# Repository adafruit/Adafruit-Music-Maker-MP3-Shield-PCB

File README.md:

# Adafruit Music Maker MP3 Shields PCB

&nbsp; <br />
Click to purchase from the Adafruit Shop:
- [With 3W Amp](https://www.adafruit.com/product/1788)
- [Without 3W Amp](https://www.adafruit.com/product/1790)

These powerful shields feature the VS1053, an encoding/decoding (codec) chip that can decode a wide variety of audio formats such as MP3, AAC, Ogg Vorbis, WMA, MIDI, FLAC, WAV (PCM and ADPCM). They can also be used to record audio in both PCM (WAV) and compressed Ogg Vorbis. You can do all sorts of stuff with the audio as well such as adjusting bass, treble, and volume digitally.

All this functionality is implemented in a light-weight SPI interface so that any Arduino can play audio from an SD card. There's also a special MIDI mode that you can boot the chip into that will read 'classic' 31250Kbaud MIDI data from an Arduino pin and act like a synth/drum machine - there are dozens of built-in drum and sample effects! But the chip is a pain to solder, and needs a lot of extras. That's why we spun up the best shields, perfect for use with any Adafruit Metro or Arduino Uno, Leonardo or Mega.

There are two versions of the shield: the first has stereo line/headphone output. There is also a version with a 3W/channel class-D stereo speaker amplifier for easy use in projects that need to be loud.

Yjis repo contains PCB files for the Adafruit Music Maker VS1053 (MP3/MIDI/WAV/Ogg...) Shields for Arduino

Format is EagleCAD schematic and board layout

For more details, check out the product pages at

-----> https://www.adafruit.com/product/1788

-----> https://www.adafruit.com/product/1790

Revision history:

* As of Aug 23, 2023 - we've updated this PCB with Adafruit Pinguin to make a lovely and legible silkscreen. We've also updated the music maker to use the 2x3 SPI header instead of pins 11/12/13  and the terminal blocks now come pre-soldered on.
* Aug 20, 2014: We updated the analog section to have more filtering, which should improve audio output quality (even more!) There are no wiring or code changes.

### License

Adafruit invests time and resources providing this open source design, please support Adafruit and open-source hardware by purchasing products from [Adafruit](https://www.adafruit.com)!

All text above must be included in any redistribution

Designed by Limor Fried/Ladyada for Adafruit Industries.
Creative Commons Attribution/Share-Alike, all text above must be included in any redistribution. 
See license.txt for additional information.

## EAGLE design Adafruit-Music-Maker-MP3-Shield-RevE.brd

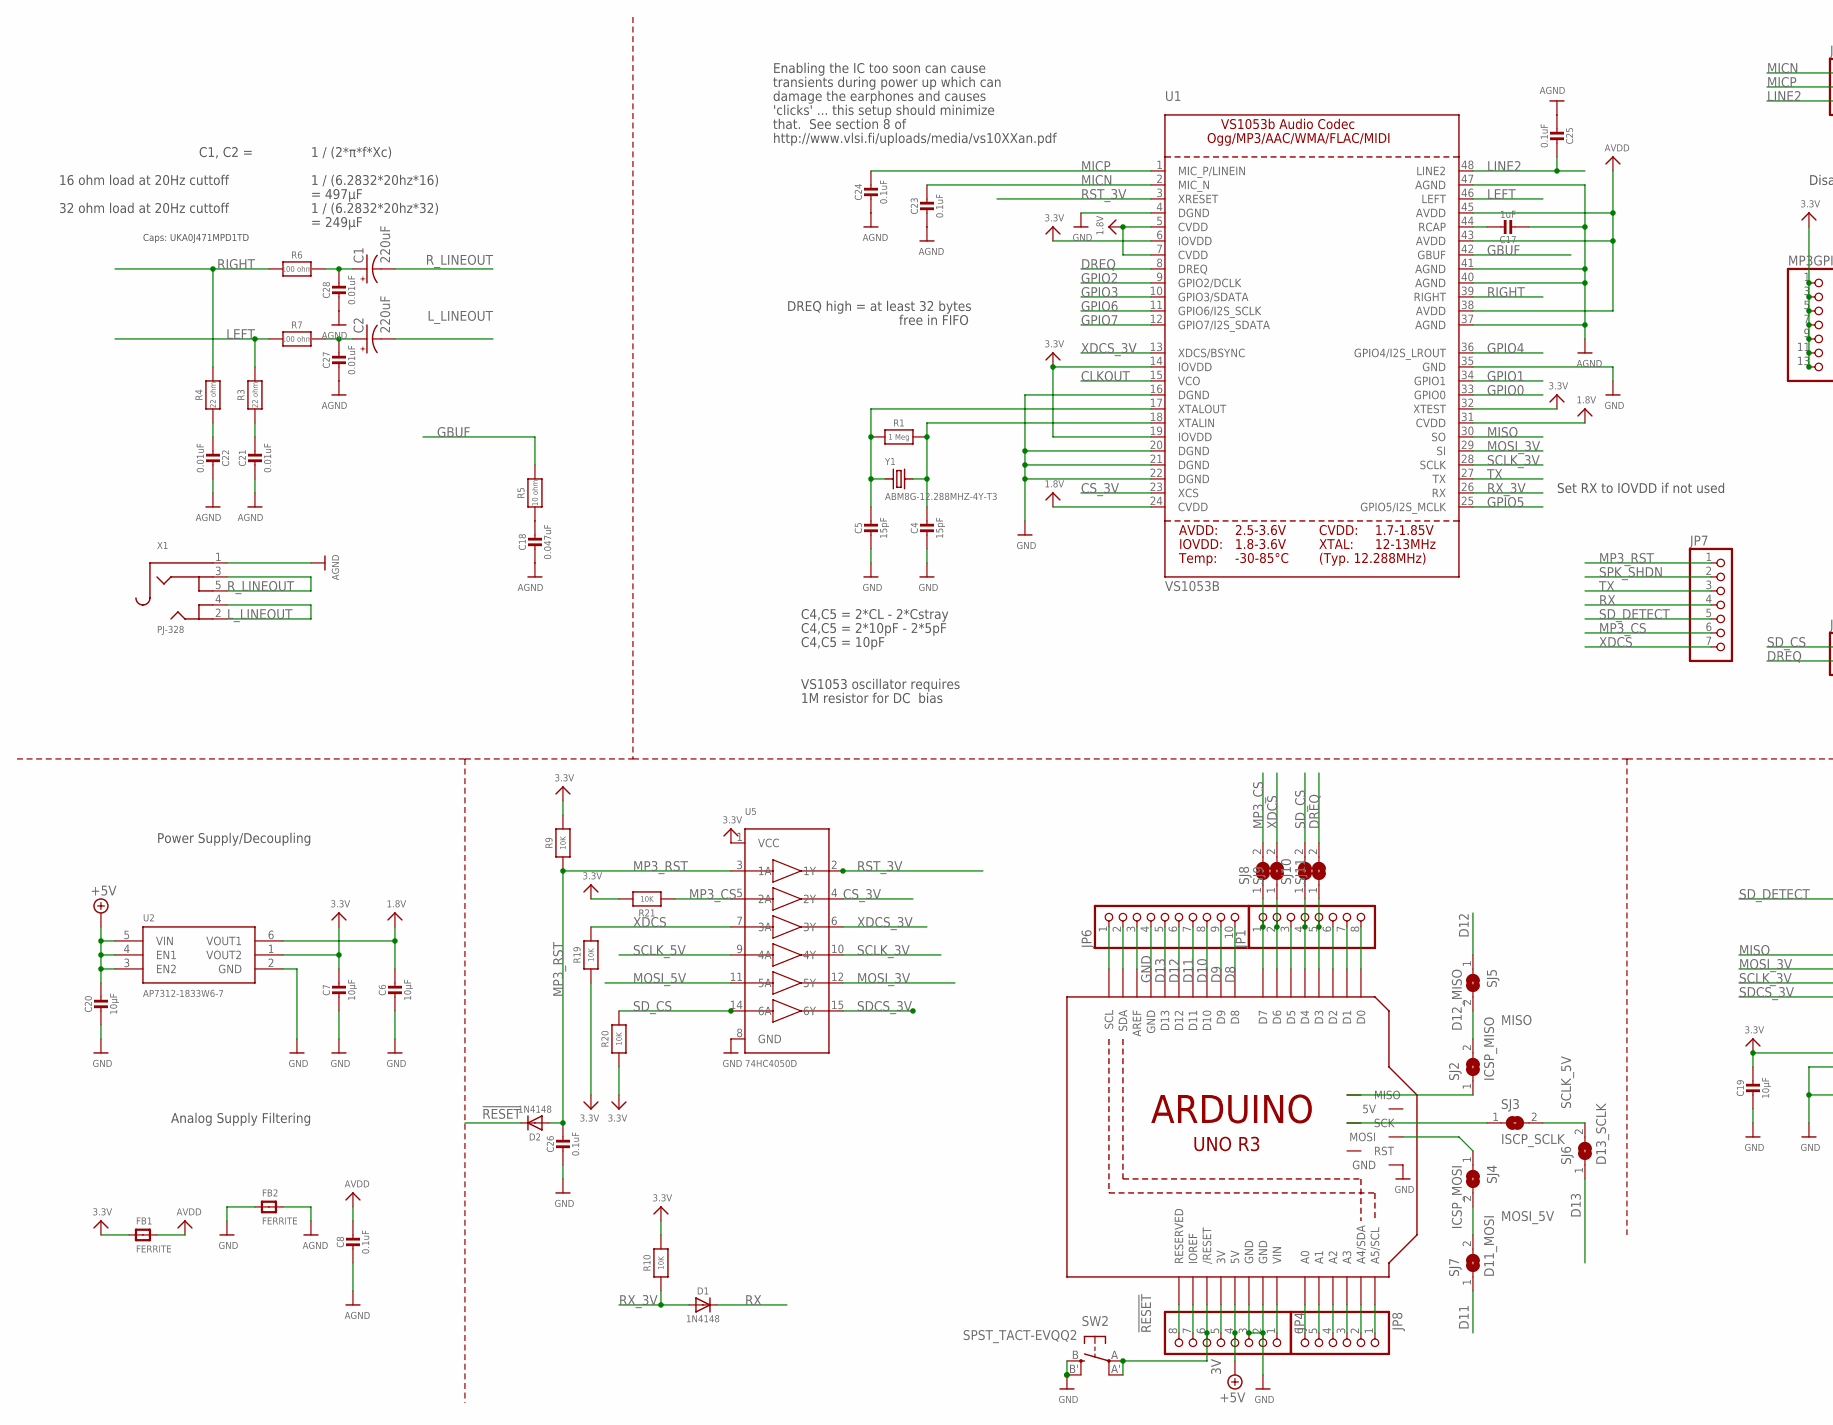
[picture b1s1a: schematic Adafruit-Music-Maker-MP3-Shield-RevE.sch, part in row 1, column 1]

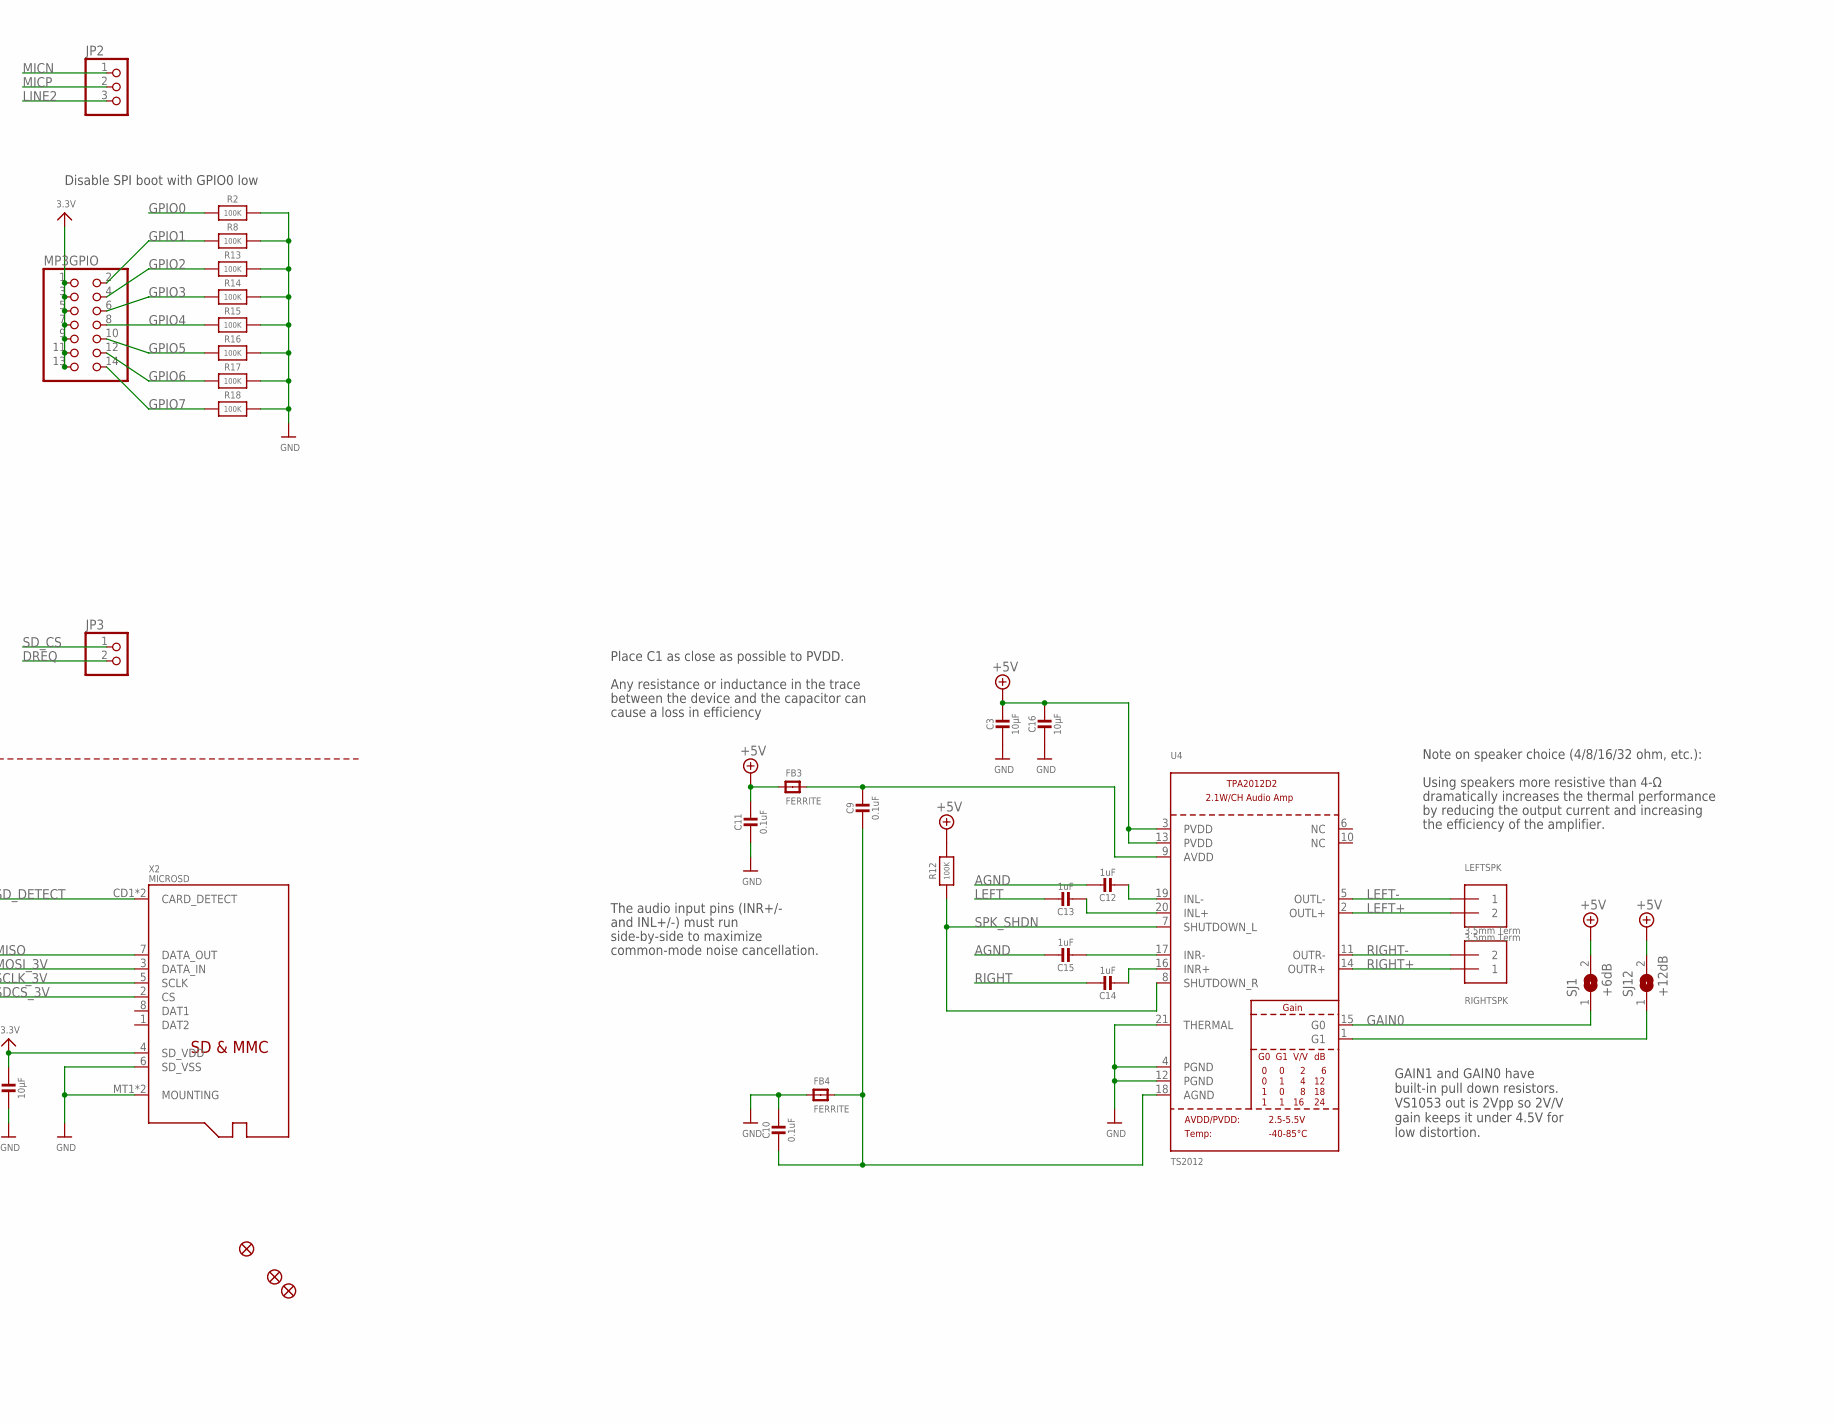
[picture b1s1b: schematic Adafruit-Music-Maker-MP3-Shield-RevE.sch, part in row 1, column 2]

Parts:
C1, C2: 220uF; PANASONIC_C
C3, C6, C7, C16, C19, C20: 10µF; 0805-NO
C4, C5: 15pF; 0603-NO
C8, C9, C10, C11, C23, C24, C25, C26: 0.1uF; 0603-NO
C12, C13, C14, C15, C17: 1uF; 0603-NO
C18: 0.047uF; 0603-NO
C21, C22, C27, C28: 0.01uF; 0603-NO
D1, D2: 1N4148; SOD-323
FB1, FB2, FB3, FB4: FERRITE; 0603-NO
FID1, FID2, FID3: FIDUCIAL_1MM
JP1, JP4: PINHD-1X8CLEANBIG; 1X08-CLEANBIG
JP2: PINHD-1X3CB; 1X03-CLEANBIG
JP3: HEADER-1X2ROUND; 1X02_ROUND
JP6: HEADER-1X1070MIL; 1X10_ROUND70
JP7: HEADER-1X770MIL; 1X07_ROUND_70
JP8: PINHD-1X6CB; 1X06-CLEANBIG
LEFTSPK: 3.5mm Term; TERMBLOCK_1X2-3.5MM
MP3GPIO: HEADER-2X7_ROUND_70MIL; 2X07_ROUND_70MIL
R1: 1 Meg; 0603-NO
R2, R8, R12, R13, R14, R15, R16, R17, R18: 100K; 0603-NO
R3, R4: 22 ohm; 0603-NO
R5: 10 ohm; 0603-NO
R6, R7: 100 ohm; 0603-NO
R9, R10, R19, R20, R21: 10K; 0603-NO
RIGHTSPK: 3.5mm Term; TERMBLOCK_1X2-3.5MM
SJ1: +6dB; SOLDERJUMPER_ARROW_NOPASTE
SJ2: ICSP_MISO; SOLDERJUMPER_CLOSEDWIRE
SJ3: ISCP_SCLK; SOLDERJUMPER_CLOSEDWIRE
SJ4: ICSP_MOSI; SOLDERJUMPER_CLOSEDWIRE
SJ5: D12_MISO; SOLDERJUMPER_ARROW_NOPASTE
SJ6: D13_SCLK; SOLDERJUMPER_ARROW_NOPASTE
SJ7: D11_MOSI; SOLDERJUMPER_ARROW_NOPASTE
SJ8, SJ9, SJ10, SJ11: SOLDERJUMPERCLOSED; SOLDERJUMPER_CLOSEDWIRE
SJ12: +12dB; SOLDERJUMPER_ARROW_NOPASTE
SW2: SPST_TACT-EVQQ2; EVQ-Q2
U1: VS1053B; LQFP48
U2: AP7312-1833W6-7; SOT23-6
U4: TS2012; WQFN20
U5: 74HC4050D; SOIC16
U$41: ARDUINO_R3_ICSP; ARDUINOR3_ICSP
X1: PJ-328; PJ-328-5
X2: MICROSD
Y1: ABM8G-12.288MHZ-4Y-T3; CRYSTAL_3.2X2.5

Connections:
1.8V: C6.1, U1.5 (CVDD), U1.7 (CVDD), U1.24 (CVDD), U1.31 (CVDD), U2.6 (VOUT1)
3.3V: C7.1, C19.1, FB1.1, MP3GPIO.1, MP3GPIO.3, MP3GPIO.5, MP3GPIO.7, MP3GPIO.9, MP3GPIO.11, MP3GPIO.13, R9.2, R10.2, R19.1, R20.1, R21.2, U1.6 (IOVDD), U1.14 (IOVDD), U1.19 (IOVDD), U1.32 (XTEST), U2.1 (VOUT2), U5.1 (VCC), X2.4 (SD_VDD)
3V: JP4.5, U$41.3V
!RESET: D2.C, JP4.6, SW2.A, SW2.A' (P1), U$41.RESET (/RESET)
+5V: C3.1, C11.1, C16.1, C20.1, FB3.1, JP4.4, R12.2, SJ1.2, SJ12.2, U2.3 (EN2), U2.4 (EN1), U2.5 (VIN), U4.3 (PVDD), U4.13 (PVDD), U$41.5V
A0: JP8.6, U$41.A0
A1: JP8.5, U$41.A1
A2: JP8.4, U$41.A2
A3: JP8.3, U$41.A3
A4: JP8.2, U$41.A4 (A4/SDA)
A5: JP8.1, U$41.A5 (A5/SCL)
AGND: C8.2, C12.1, C15.1, C17.2, C18.2, C21.2, C22.2, C23.2, C24.2, C25.2, C27.2, C28.2, FB2.2, U1.37 (AGND), U1.40 (AGND), U1.41 (AGND), U1.47 (AGND), X1.1
AREF: JP6.3, U$41.AREF
AVDD: C8.1, FB1.2, U1.38 (AVDD), U1.43 (AVDD), U1.45 (AVDD)
CLKOUT: U1.15 (VCO)
CS_3V: U1.23 (XCS), U5.4 (2Y)
D0: JP1.8, U$41.D0
D1: JP1.7, U$41.D1
D2: JP1.6, U$41.D2
D3: JP1.5, SJ11.1, U$41.D3
D4: JP1.4, SJ10.1, U$41.D4
D5: JP1.3, U$41.D5
D6: JP1.2, SJ9.1, U$41.D6
D7: JP1.1, SJ8.1, U$41.D7
D8: JP6.10, U$41.D8
D9: JP6.9, U$41.D9
D10: JP6.8, U$41.D10
D11: JP6.7, SJ7.1, U$41.D11
D12: JP6.6, SJ5.1, U$41.D12
D13: JP6.5, SJ6.1, U$41.D13
DREQ: JP3.2, SJ11.2, U1.8 (DREQ)
GAIN0: SJ1.1, U4.15 (G0)
GBUF: R5.1, U1.42 (GBUF)
GND: C3.2, C4.2, C5.2, C6.2, C7.2, C10.1, C11.2, C16.2, C19.2, C20.2, C26.2, FB2.1, FB4.1, JP4.2, JP4.3, JP6.4, R2.2, R8.2, R13.2, R14.2, R15.2, R16.2, R17.2, R18.2, SW2.B (S), SW2.B' (S1), U1.4 (DGND), U1.16 (DGND), U1.20 (DGND), U1.21 (DGND), U1.22 (DGND), U1.35 (GND), U2.2 (GND), U4.4 (PGND), U4.12 (PGND), U4.21 (THERMAL), U5.8 (GND), U$41.GND, U$41.GND@1 (GND), U$41.GND@2 (GND), U$41.GND@3 (GND), X2.6 (SD_VSS), X2.MT1 (MOUNTING), X2.MT2 (MOUNTING)
GPIO0: R2.1, U1.33 (GPIO0)
GPIO1: MP3GPIO.2, R8.1, U1.34 (GPIO1)
GPIO2: MP3GPIO.4, R13.1, U1.9 (GPIO2/DCLK)
GPIO3: MP3GPIO.6, R14.1, U1.10 (GPIO3/SDATA)
GPIO4: MP3GPIO.8, R15.1, U1.36 (GPIO4/I2S_LROUT)
GPIO5: MP3GPIO.10, R16.1, U1.25 (GPIO5/I2S_MCLK)
GPIO6: MP3GPIO.12, R17.1, U1.11 (GPIO6/I2S_SCLK)
GPIO7: MP3GPIO.14, R18.1, U1.12 (GPIO7/I2S_SDATA)
IOREF: JP4.7, U$41.IOREF
LEFT: C13.1, R3.1, R7.2, U1.46 (LEFT)
LEFT+: LEFTSPK.2, U4.2 (OUTL+)
LEFT-: LEFTSPK.1, U4.5 (OUTL-)
LEFT_FILTERED: C2.+, C27.1, R7.1
LINE2: C25.1, JP2.3, U1.48 (LINE2)
L_LINEOUT: C2.-, X1.2, X1.4
MICN: C23.1, JP2.1, U1.2 (MIC_N)
MICP: C24.1, JP2.2, U1.1 (MIC_P/LINEIN)
MISO: SJ2.2, SJ5.2, U1.30 (SO), X2.7 (DATA_OUT)
MISO_ICSP: SJ2.1, U$41.MISO
MOSI_3V: U1.29 (SI), U5.12 (5Y), X2.3 (DATA_IN)
MOSI_5V: SJ4.2, SJ7.2, U5.11 (5A)
MOSI_ICSP: SJ4.1, U$41.MOSI
MP3_CS: JP7.6, R21.1, SJ8.2, U5.5 (2A)
MP3_RST: C26.1, D2.A, JP7.1, R9.1, U5.3 (1A)
unnamed: C5.1, R1.1, U1.17 (XTALOUT), Y1.1
unnamed: C4.1, R1.2, U1.18 (XTALIN), Y1.2
unnamed: C21.1, R3.2
unnamed: C22.1, R4.2
unnamed: C13.2, U4.20 (INL+)
unnamed: C12.2, U4.19 (INL-)
unnamed: C15.2, U4.17 (INR-)
unnamed: C14.2, U4.16 (INR+)
unnamed: C9.2, C10.2, FB4.2, U4.18 (AGND)
unnamed: C9.1, FB3.2, U4.9 (AVDD)
unnamed: SJ12.1, U4.1 (G1)
unnamed: C17.1, U1.44 (RCAP)
unnamed: C18.1, R5.2
NC: JP4.8, U$41.RESERVED
RIGHT: C14.1, R4.1, R6.2, U1.39 (RIGHT)
RIGHT+: RIGHTSPK.1, U4.14 (OUTR+)
RIGHT-: RIGHTSPK.2, U4.11 (OUTR-)
RIGHT_FILTERED: C1.+, C28.1, R6.1
RST_3V: U1.3 (XRESET), U5.2 (1Y)
RX: D1.C, JP7.4
RX_3V: D1.A, R10.1, U1.26 (RX)
R_LINEOUT: C1.-, X1.3, X1.5
SCK_ICSP: SJ3.1, U$41.SCK
SCL: JP6.1, U$41.SCL
SCLK_3V: U1.28 (SCLK), U5.10 (4Y), X2.5 (SCLK)
SCLK_5V: SJ3.2, SJ6.2, U5.9 (4A)
SDA: JP6.2, U$41.SDA
SDCS_3V: U5.15 (6Y), X2.2 (CS)
SD_CS: JP3.1, R20.2, SJ10.2, U5.14 (6A)
SD_DETECT: JP7.5, X2.CD1 (CARD_DETECT), X2.CD2 (CARD_DETECT)
SPK_SHDN: JP7.2, R12.1, U4.7 (SHUTDOWN_L), U4.8 (SHUTDOWN_R)
TX: JP7.3, U1.27 (TX)
VIN: JP4.1, U$41.VIN
XDCS: JP7.7, R19.2, SJ9.2, U5.7 (3A)
XDCS_3V: U1.13 (XDCS/BSYNC), U5.6 (3Y)

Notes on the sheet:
Analog Supply Filtering
C4,C5 = 2*CL - 2*Cstray
C4,C5 = 2*10pF - 2*5pF
C4,C5 = 10pF
VS1053 oscillator requires
1M resistor for DC bias
Set RX to IOVDD if not used
DREQ high = at least 32 bytes
Power Supply/Decoupling
transients during power up which can
damage the earphones and causes
'clicks' ... this setup should minimize
that. See section 8 of
http://www.vlsi.fi/uploads/media/vs10XXan.pdf
Enabling the IC too soon can cause
free in FIFO
Disable SPI boot with GPIO0 low
1 / (2*π*f*Xc)
16 ohm load at 20Hz cuttoff
1 / (6.2832*20hz*16)
C1, C2 =
= 497µF
32 ohm load at 20Hz cuttoff
1 / (6.2832*20hz*32)
= 249µF
Caps: UKA0J471MPD1TD
GAIN1 and GAIN0 have built-in pull down resistors. VS1053 out is 2Vpp so 2V/V gain keeps it under 4.5V for low distortion.
Place C1 as close as possible to PVDD.
Any resistance or inductance in the trace
between the device and the capacitor can
cause a loss in efficiency
Using speakers more resistive than 4-Ω
dramatically increases the thermal performance
by reducing the output current and increasing
the efficiency of the amplifier.
Note on speaker choice (4/8/16/32 ohm, etc.):
The audio input pins (INR+/-
and INL+/-) must run
side-by-side to maximize
common-mode noise cancellation.

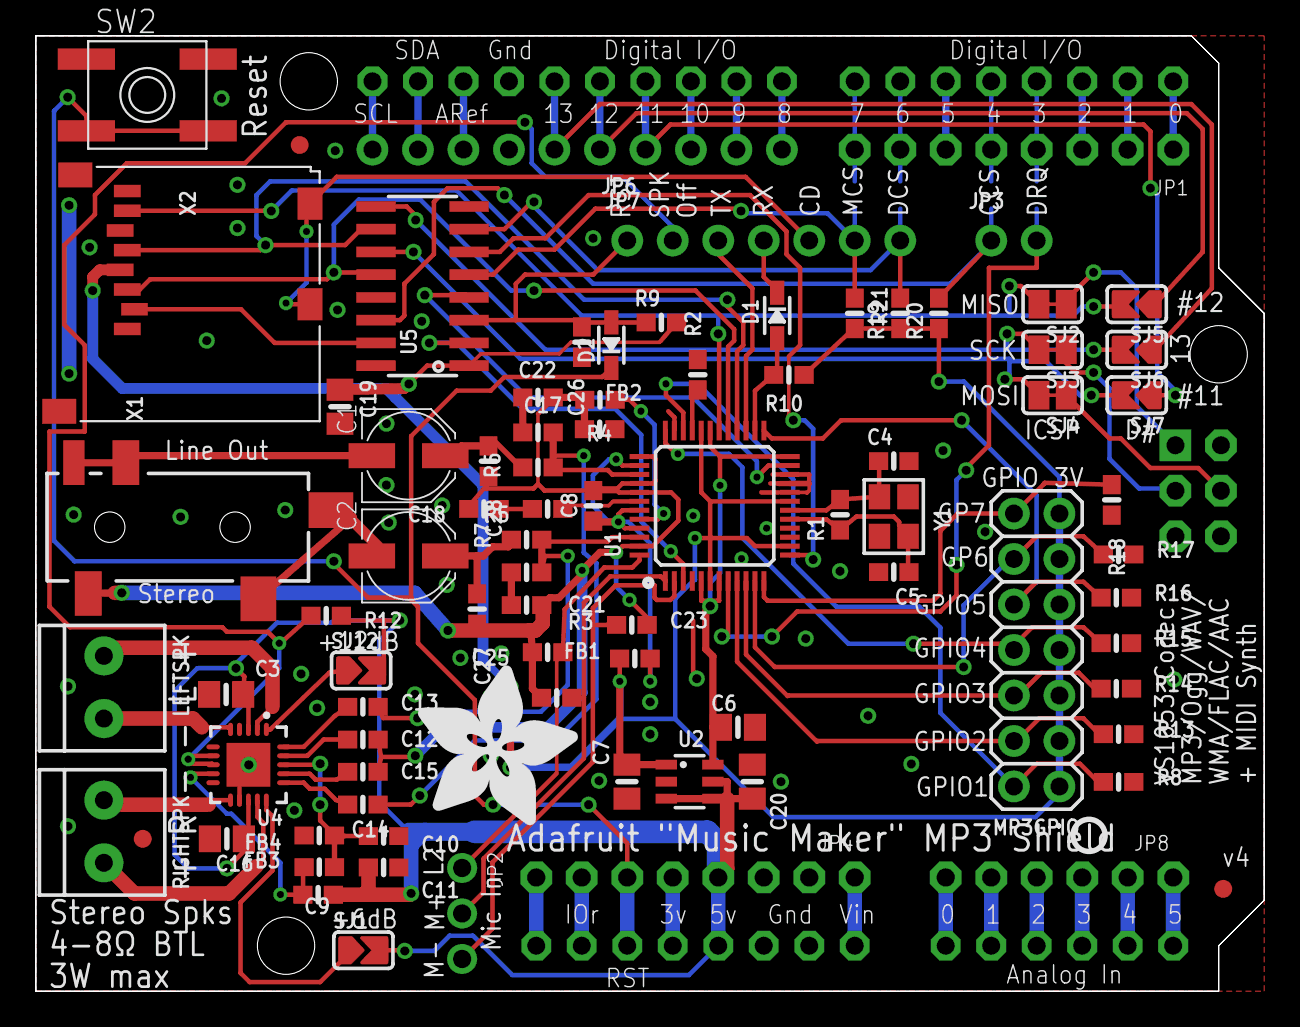
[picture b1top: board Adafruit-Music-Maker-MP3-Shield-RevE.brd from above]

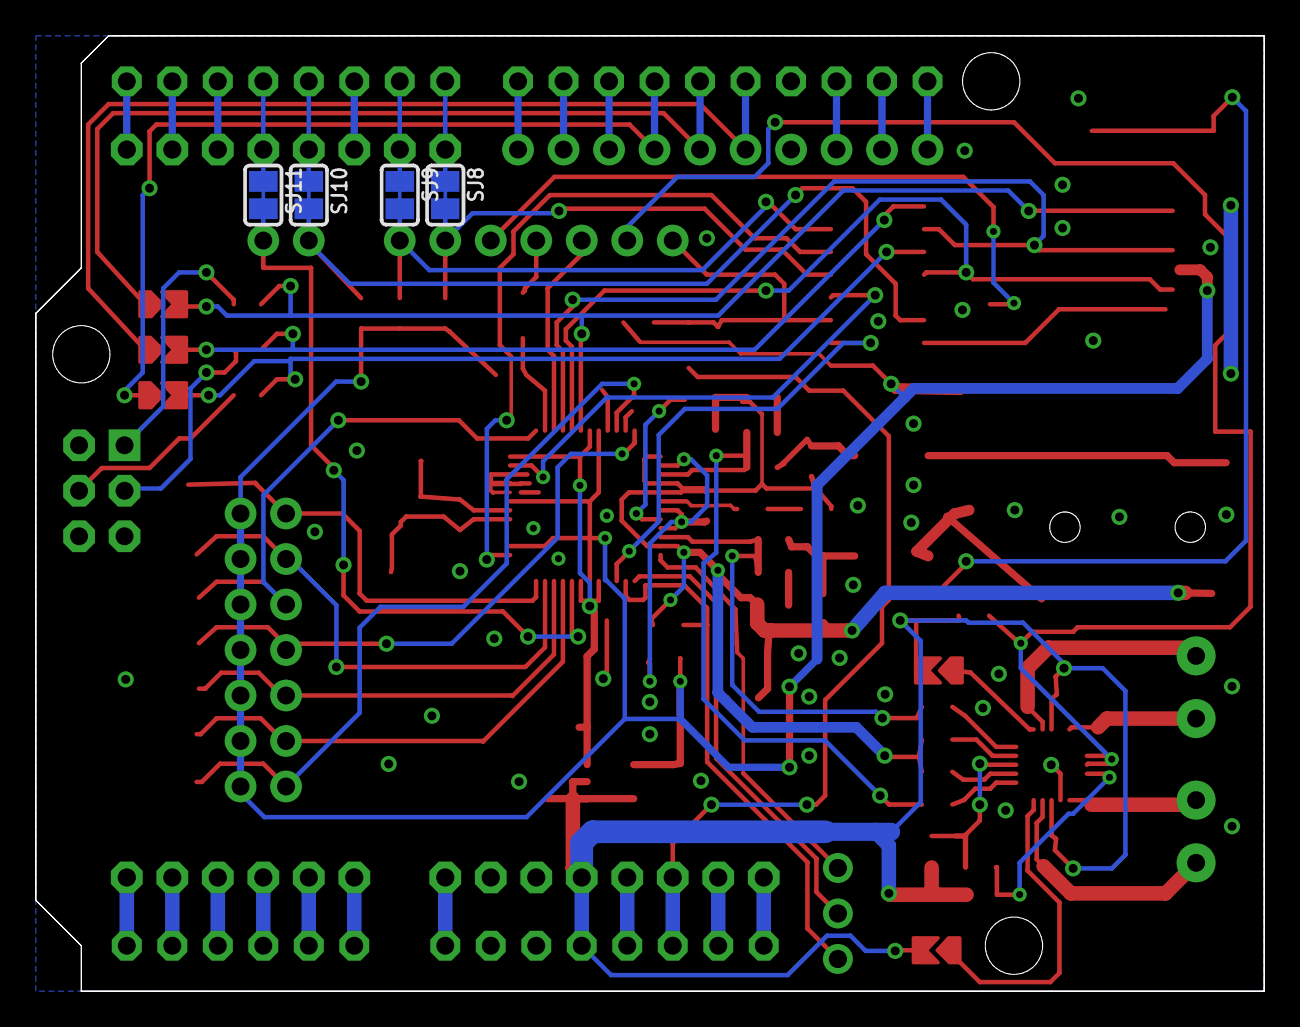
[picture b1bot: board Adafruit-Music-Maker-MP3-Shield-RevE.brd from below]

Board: 2 copper layers, 68.6 x 53.3 mm, 90 parts (4 on the bottom side), 92 nets.

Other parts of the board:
U$50: ADAFRUIT_9MM
U$57: PCBFEAT-REV-040

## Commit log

2015-02-20 init
2015-02-20 reamde
2024-07-12 rev e
